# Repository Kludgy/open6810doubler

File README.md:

Open 6810 Doubler for the Atari 1050 Disk Drive
===============================================

This repository holds KiCad files for a PCB that, when used in conjunction with a custom Atari 1050 ROM, increases the available SRAM in a stock Atari 1050 Disk Drive from 128 bytes to 256 bytes. The 256 bytes of RAM is presumably enough to fit an entire sector's worth of data. Far more information can be found here: http://blog.3b2.sk/igi/post/Atari-1050-ICD-US-doubler.aspx

BOM: 
* 2x MCM6810.
* 2x Pin Header Strips to socket the PCB into the original 6810 location on the mainboard.
* 1x 24-pin socket on the mainboard as you wish.

Be advised the PCB will need to be socketed high enough to clear other components on the board.

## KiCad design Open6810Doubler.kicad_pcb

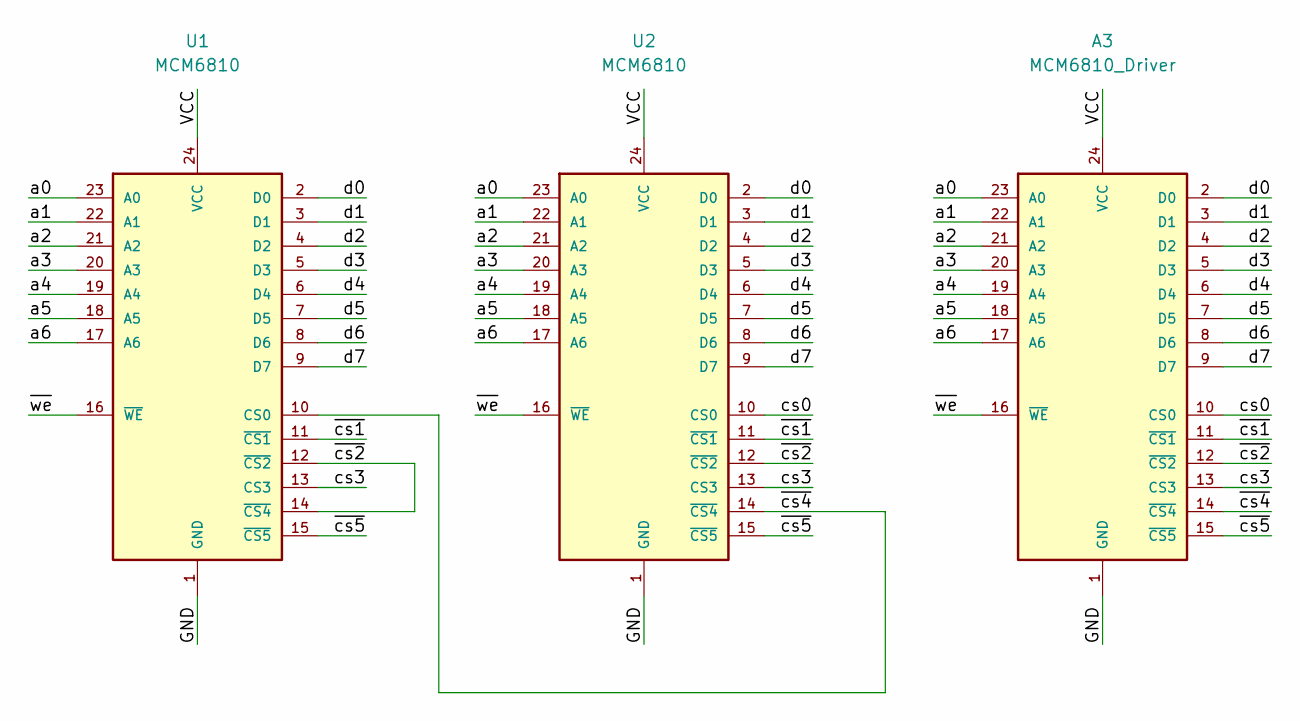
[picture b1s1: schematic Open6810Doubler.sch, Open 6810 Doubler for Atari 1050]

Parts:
A3: MCM6810_Driver; DIP-24_W15.24mm_LongPads
U1, U2: MCM6810; DIP-24_W15.24mm_LongPads

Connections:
/GND: A3.1 (GND), U1.1 (GND), U2.1 (GND)
/VCC: A3.24 (VCC), U1.24 (VCC), U2.24 (VCC)
/a0: A3.23 (A0), U1.23 (A0), U2.23 (A0)
/a1: A3.22 (A1), U1.22 (A1), U2.22 (A1)
/a2: A3.21 (A2), U1.21 (A2), U2.21 (A2)
/a3: A3.20 (A3), U1.20 (A3), U2.20 (A3)
/a4: A3.19 (A4), U1.19 (A4), U2.19 (A4)
/a5: A3.18 (A5), U1.18 (A5), U2.18 (A5)
/a6: A3.17 (A6), U1.17 (A6), U2.17 (A6)
/cs0: A3.10 (CS0), U2.10 (CS0)
/cs3: A3.13 (CS3), U1.13 (CS3), U2.13 (CS3)
/d0: A3.2 (D0), U1.2 (D0), U2.2 (D0)
/d1: A3.3 (D1), U1.3 (D1), U2.3 (D1)
/d2: A3.4 (D2), U1.4 (D2), U2.4 (D2)
/d3: A3.5 (D3), U1.5 (D3), U2.5 (D3)
/d4: A3.6 (D4), U1.6 (D4), U2.6 (D4)
/d5: A3.7 (D5), U1.7 (D5), U2.7 (D5)
/d6: A3.8 (D6), U1.8 (D6), U2.8 (D6)
/d7: A3.9 (D7), U1.9 (D7), U2.9 (D7)
/~cs1: A3.11 (~CS1), U1.11 (~CS1), U2.11 (~CS1)
/~cs2: A3.12 (~CS2), U1.12 (~CS2), U1.14 (~CS4), U2.12 (~CS2)
/~cs4: A3.14 (~CS4), U1.10 (CS0), U2.14 (~CS4)
/~cs5: A3.15 (~CS5), U1.15 (~CS5), U2.15 (~CS5)
/~we: A3.16 (~WE~), U1.16 (~WE~), U2.16 (~WE~)

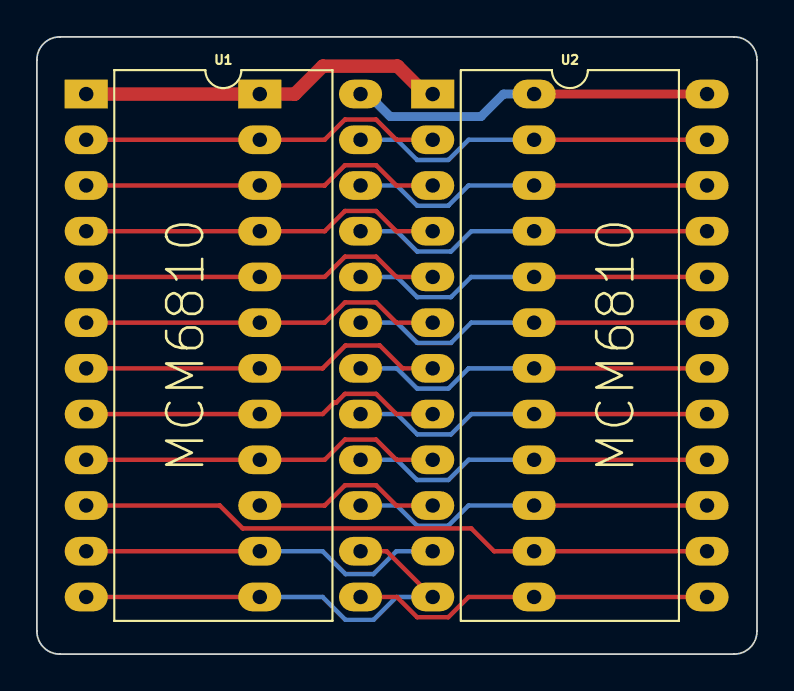
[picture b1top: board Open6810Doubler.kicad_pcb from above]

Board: 2 copper layers, 40.0 x 34.3 mm, 3 parts (0 on the bottom side), 24 nets.

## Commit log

2020-02-23 license
